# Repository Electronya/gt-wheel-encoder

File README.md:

# gt-wheel-encoder
GT Wheel Encoder Board

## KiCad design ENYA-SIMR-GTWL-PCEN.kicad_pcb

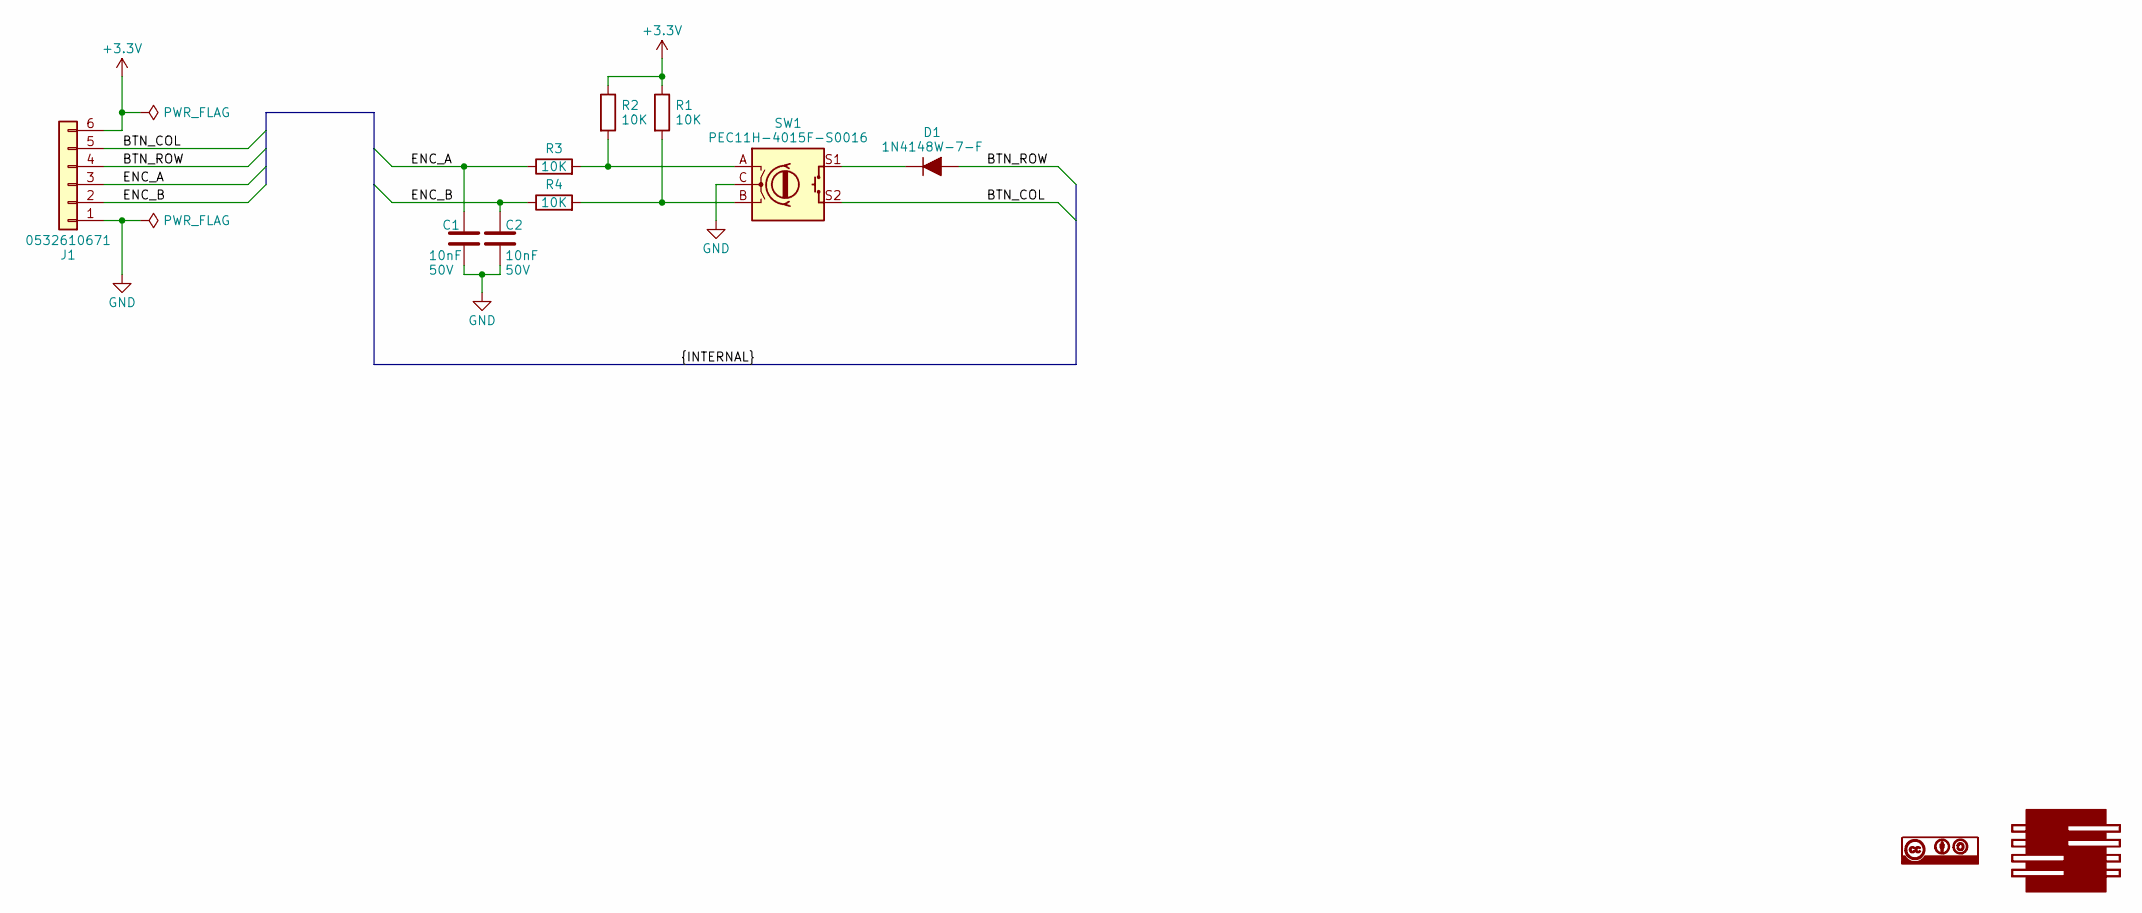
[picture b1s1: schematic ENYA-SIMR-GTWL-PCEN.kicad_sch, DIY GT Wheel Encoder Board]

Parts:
C1, C2: 10nF_CER_0603_50V; C_0603_1608Metric; Voltage Rating 50V; Manufacturer Part Number 06035C103KAT2A; Digi-Key Part Number 478-1227-1-ND
D1: 1N4148W-7-F; D_SOD-123; Manufacturer Part Number 1N4148W-7-F; Digi-Key Part Number 1N4148W-FDICT-ND
G1: Electronya_Logo; Electronya_Logo_8MM
G2: CC-BY-SA_Logo; CC-BY-SA_6MM
J1: PICO_BLADE_1x6_MALE_RA_SMD; PICO_BLADE_53261_1x6_SMD_RA_1.25MM; Manufacturer Part Number 0532610671; Digi-Key Part Number WM7624CT-ND
R1, R2, R3, R4: 10K_0603_100MW; R_0603_1608Metric; Manufacturer Part Number ERJ-3EKF1002V; Digi-Key Part Number P10.0KHCT-ND
SW1: PEC11H-4015F-S0016; PEC11H_Switch_Vertical; Manufacturer Part Number PEC11H-4015F-S0016; Digi-Key Part Number 118-PEC11H-4015F-S0016-ND

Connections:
+3.3V: J1.6, R1.1, R2.1
/BTN_COL: J1.5, SW1.S2
/BTN_ROW: D1.2 (A), J1.4
/ENC_A: C1.1, J1.3, R3.1
/ENC_B: C2.1, J1.2, R4.1
GND: C1.2, C2.2, J1.1, SW1.C
unnamed: D1.1 (K), SW1.S1
unnamed: R1.2, R4.2, SW1.B
unnamed: R2.2, R3.2, SW1.A

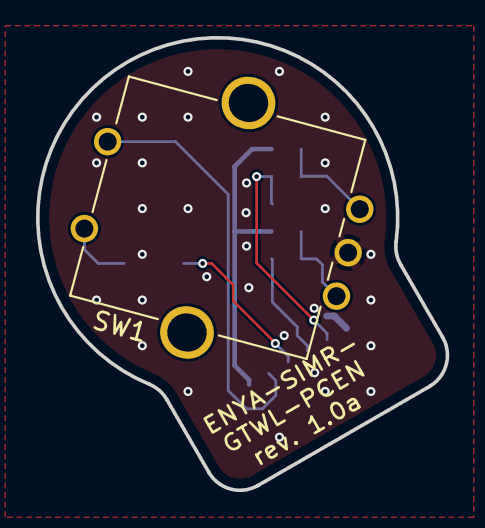
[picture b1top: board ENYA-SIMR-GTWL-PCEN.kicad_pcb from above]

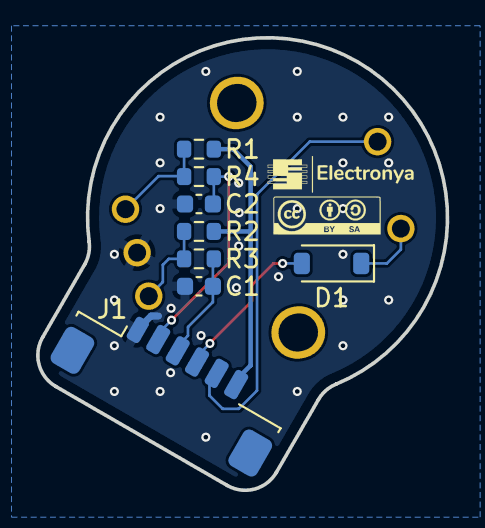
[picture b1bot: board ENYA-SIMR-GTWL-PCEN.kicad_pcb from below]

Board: 2 copper layers, 22.8 x 25.1 mm, 11 parts (10 on the bottom side), 9 nets.

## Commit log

2023-06-30 ready for tag
2023-07-01 correction button matrix diode polarity
2023-07-01 replacing silkscreen

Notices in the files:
parts and their libraries:
CC-BY-SA, creative common
